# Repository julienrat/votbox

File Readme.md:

Vot'Box - boitier de vote 
=

----
##Fonctionnement
### Connection à un réseau Wifi
Au démarrage si le boitier ne reconnait pas de wifi, les 2 leds (rouge et vertes) se metent à clignotter signalant que ce dernier est en mode de configuration.

Afin de connecter celui-ci à un réseau Wifi, il faut se connecter sur le SSID (Vot_box_XXXXXX ) et se rendre à l'adresse 192.168.4.1 pour accéder à l'interface de configuration.

Cliquez sur **Configure Wifi**

Sélectionnez le réseau puis entrez votre mot de passe

Pour effacer les réseaux enregistrés, allumez le boitier en maintenant la touche **#** enfoncée.
###Utilisation
A l'allumage du boitier, la led verte se met à clignotter indiquant que celui-ci est en train de se connecter  . Si celui-ci trouve son réseau, la led arrete de clignotter et devient fixe . Sinon, le boitier se met en point d'accès (les leds rouges et vertes clignottent )

Pour voter, faites votre choix (chiffres et lettres). à la pression sur une touche, la led rouge se met à clignotter indiquant que le vote est mémorisé . Pour modifier en cas d'erreur, appuyez sur la touche * . La led rouge s'eteint et permet de sélectionner une autre réponse .

Pour valider et envoyer votre vote au serveur, appuyez sur la touche #. La led rouge arrete de clignotter et devient fixe .  Il est alors impossible d'envoyer un autre vote.

###Remise à zero
Pour permettre un autre vote, l'animateur doit réinitialiser les boitiers en envoyant la requette : http://adresse_ip_boitier/RAZ la led rouge s'éteint et permet alors un nouveau vote.

###Messages

Leds | Messages
------------ | --------------
 | Le boitier ne parvient pas à se connecter, Mode configuration en point d'accès 
 | Le boitier est en train de se connecter
 | Le boitier est connecté et est prêt à être utilisé 
 | Vote enregistré dans la mémoire mais pas envoyé au serveur
 | Vote effectué, attente de remise à zero

###Boitier 3D

###Schema de cablage
Fritzing | Eagle
---------|---------
 |  

###Vue PCB
Bottom | Top
---------|---------
 |

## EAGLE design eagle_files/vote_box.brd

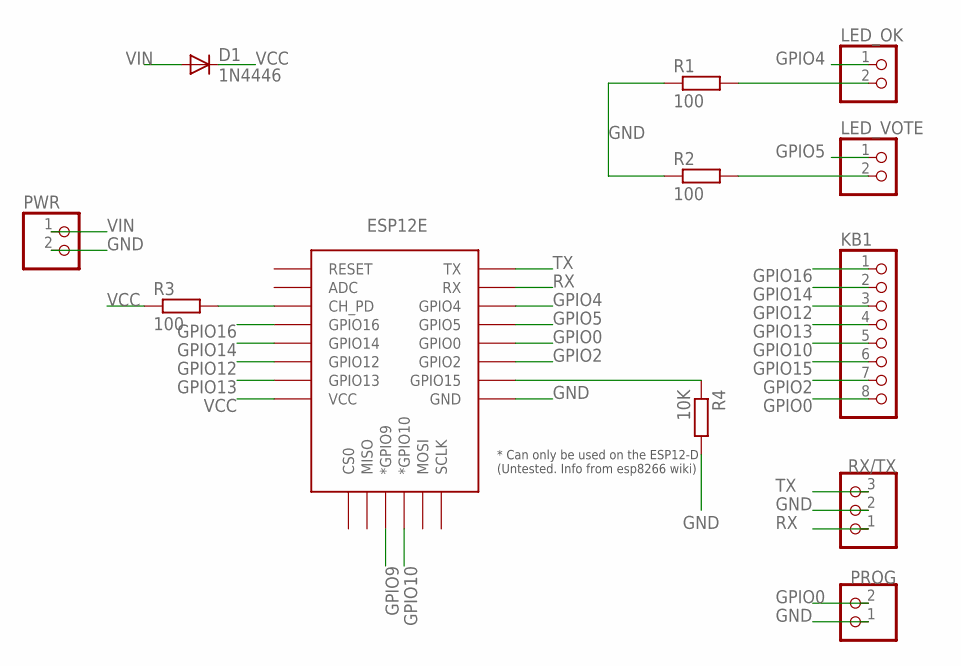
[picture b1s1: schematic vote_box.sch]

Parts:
D1: 1N4446; DO35-10
ESP12E: ESP12ESMD; ESP12E-SMD
KB1: PINHD-1X8; 1X08
LED_OK: PINHD-1X2; 1X02
LED_VOTE: PINHD-1X2; 1X02
PROG: PINHD-1X2; 1X02
PWR: PINHD-1X2; 1X02
R1, R2, R3: 100; 0207/10
R4: 10K; 0207/10
RX/TX: PINHD-1X3; 1X03

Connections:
GND: ESP12E.GND, PROG.1, PWR.2, R1.1, R2.1, R4.2, RX/TX.2
GPIO0: ESP12E.GPIO0, KB1.8, PROG.2
GPIO2: ESP12E.GPIO2, KB1.7
GPIO4: ESP12E.GPIO4, LED_OK.1
GPIO5: ESP12E.GPIO5, LED_VOTE.1
GPIO9: ESP12E.GPIO9 (*GPIO9)
GPIO10: ESP12E.GPIO10 (*GPIO10), KB1.5
GPIO12: ESP12E.GPIO12, KB1.3
GPIO13: ESP12E.GPIO13, KB1.4
GPIO14: ESP12E.GPIO14, KB1.2
GPIO15: ESP12E.GPIO15, KB1.6, R4.1
GPIO16: ESP12E.GPIO16, KB1.1
unnamed: ESP12E.CH_PD, R3.2
unnamed: LED_VOTE.2, R2.2
unnamed: LED_OK.2, R1.2
RX: ESP12E.RXD0 (RX), RX/TX.1
TX: ESP12E.TXD0 (TX), RX/TX.3
VCC: D1.C, ESP12E.VCC, R3.1
VIN: D1.A, PWR.1

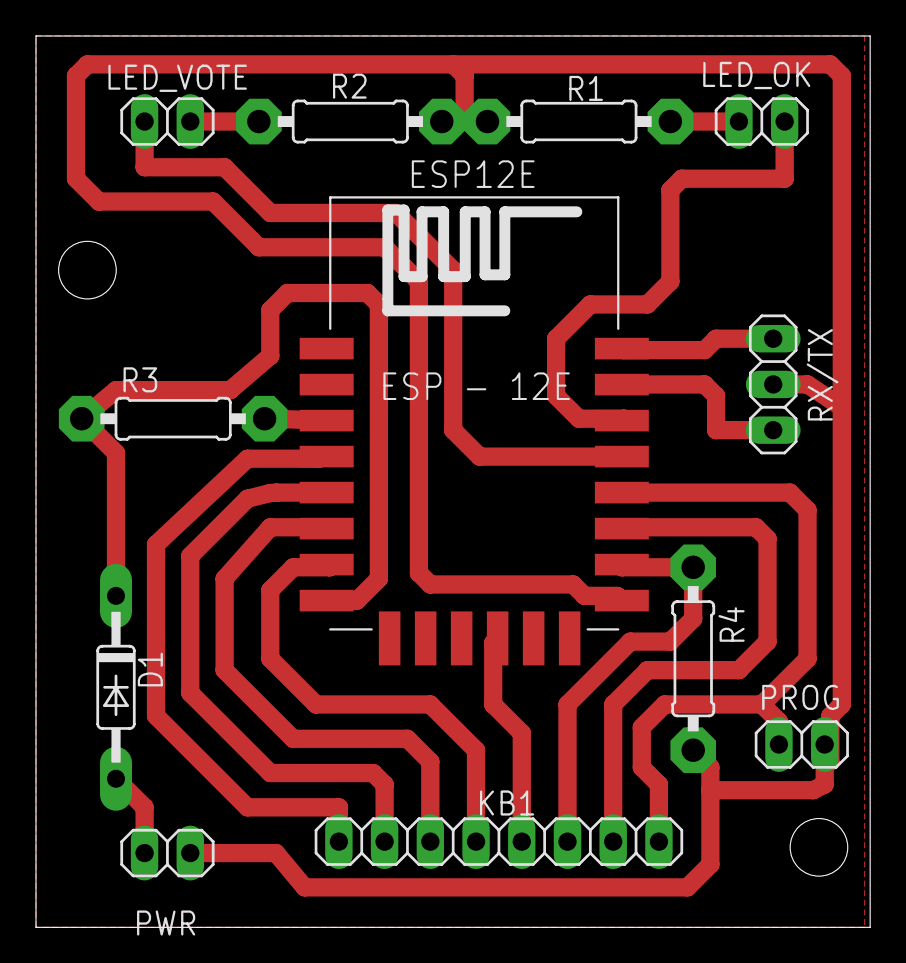
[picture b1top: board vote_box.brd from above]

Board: 2 copper layers, 46.3 x 49.5 mm, 12 parts (0 on the bottom side), 18 nets.

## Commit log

2016-05-02 + ‘.sparkleshare’ + ‘SparkleShare.txt’
2016-05-02 + ‘code_esp8266/’
2016-05-02 + ‘code_esp8266/Votbox/Votbox.ino’ + ‘code_esp8266/Votbox_autoconnect/Votbox_autoconnect.ino’
2016-05-02 + ‘eagle_files/’
2016-05-02 + ‘3D_printed_case/’
2016-05-02 + ‘3D_printed_case/vote_box.dxf’ + ‘3D_printed_case/votebox.scad’
2016-05-02 + ‘eagle_files/vote_box.brd’ + ‘eagle_files/vote_box.sch’
2016-05-02 / ‘code_esp8266/Votbox_autoconnect/Votbox_autoconnect.ino’
2016-05-02 + ‘Readme.txt’
2016-05-02 / ‘Readme.txt’
2016-05-02 < ‘Readme.txt’ > ‘Readme.md’
2016-05-02 / ‘Readme.md’
2016-05-02 + ‘images/’
2016-05-02 + ‘images/accueil.png’ + ‘images/leds_ap.png’ + ‘images/leds_connect.png’ + ‘images/leds_ok.png’ + ‘images/leds_vote_mem.png’ + ‘images/selection.png’
2016-05-02 + ‘images/leds_voted.png’
2016-05-02 + ‘3D_printed_case/#vote_box.dxf’
2016-05-02 - ‘3D_printed_case/#vote_box.dxf’ / ‘3D_printed_case/vote_box.dxf’
2016-05-02 / ‘3D_printed_case/vote_box.dxf’
2016-05-02 / ‘3D_printed_case/#vote_box.dxf’
2016-05-02 / ‘3D_printed_case/votebox.scad’
2016-05-02 + ‘3D_printed_case/votebox.stl’
2016-05-02 + ‘3D_printed_case/votebox_capot.stl’
2016-05-02 + ‘3D_printed_case/votebox_fond.stl’
2016-05-02 / ‘3D_printed_case/votebox.stl’
2016-05-02 + ‘3D_printed_case/box’
2016-05-02 + ‘3D_printed_case/box.png’
2016-05-02 < ‘3D_printed_case/box.png’ > ‘images/box.png’
2016-05-02 - ‘3D_printed_case/box’
2016-05-02 / ‘code_esp8266/Votbox/Votbox.ino’
2016-05-03 - ‘3D_printed_case/votebox.stl’ - ‘3D_printed_case/votebox_capot.stl’ - ‘3D_printed_case/votebox_fond.stl’
2016-05-03 + ‘New Folder/’
2016-05-03 < ‘New Folder/’ > ‘fritzing/’
2016-05-03 + ‘fritzing/votbox.fzz’
2016-05-03 / ‘fritzing/votbox.fzz’
2016-05-03 + ‘images/votbox_bb.png’
2016-05-03 / ‘images/votbox_bb.png’
2016-05-03 + ‘images/schema.png’
2016-06-29 + ‘images/shema_photoR.png’
2016-07-31 + ‘3D_printed_case/jeton.scad’
2016-08-10 + ‘images/vote_box_bot.png’ + ‘images/vote_box_top.png’
2016-08-10 / ‘images/leds_vote_mem.png’
2016-08-10 / ‘images/leds_voted.png’
2016-08-10 / ‘images/leds_ok.png’
2016-08-10 / ‘images/leds_connect.png’
2016-08-10 / ‘images/leds_ap.png’
2016-08-10 / ‘images/vote_box_top.png’
2016-08-10 / ‘images/vote_box_bot.png’
